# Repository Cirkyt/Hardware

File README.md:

# Hardware
## This branch contains all electrical hardware projects
All projects, unless otherwise stated, are created using EagleCAD PCB v7.2.0 design software:
  - http://www.cadsoftusa.com/download-eagle/

#### Contents
  - HeartRateSensor Eval Board - Si1141
    - Evaluation board for the Si1141 optical sensor as a heart rate sensor.
  - SmartWatch PCB
    - Top level PCB for the smart watch project.

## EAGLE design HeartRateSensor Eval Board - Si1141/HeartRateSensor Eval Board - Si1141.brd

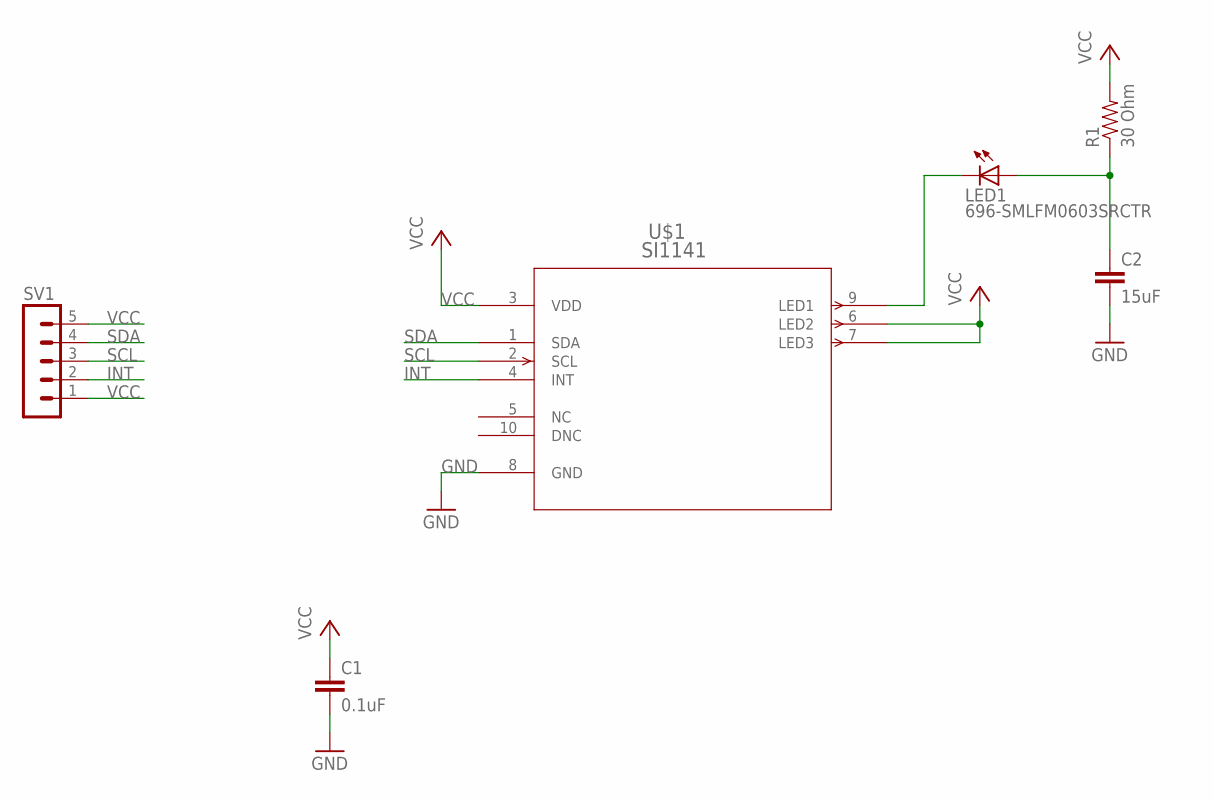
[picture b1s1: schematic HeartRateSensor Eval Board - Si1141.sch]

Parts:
C1: 0.1uF; 0603-CAP
C2: 15uF; 0603-CAP
LED1: 696-SMLFM0603SRCTR; CHIP-LED0603
R1: 30 Ohm; 0603
SV1: MA05-1
U$1: SI1141; QFN10

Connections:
GND: C1.2, C2.2, U$1.8 (GND)
INT: SV1.2, U$1.4 (INT)
unnamed: LED1.C, U$1.9 (LED1)
unnamed: C2.1, LED1.A, R1.1
SCL: SV1.3, U$1.2 (SCL)
SDA: SV1.4, U$1.1 (SDA)
VCC: C1.1, R1.2, SV1.1, SV1.5, U$1.3 (VDD), U$1.6 (LED2), U$1.7 (LED3)

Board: 2 copper layers, 6 parts (0 on the bottom side), 7 nets, no tracks yet.

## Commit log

2015-01-22 Heart rate sensor evaluation board project started
    This project is for an evaluation board to evaluate the Si1141 as a
    heart rate sensor.
2015-01-22 Finished board layout.
2015-01-23 Updated board silkscreen.
2015-02-02 Startedatch Project
2015-02-02 Revert "Startedatch Project"
    This reverts commit 9ba081d256646f31a8cb63cde6259c4e4320cdb6.
2015-02-17 Started 'SmartWatch' PCB
    Started 'SmartWatch' PCB project. Currently gathering all of the correct
    components from various part libraries.
2015-02-17 Schematic update.
    Added and connected antenna and top,right,bottom of Nordic IC

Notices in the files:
parts and their libraries:
SparkFun-Resistors: Licensing: Creative Commons ShareAlike 4.0 International - https://creativecommons.org/licenses/by-sa/4.0
